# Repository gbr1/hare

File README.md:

# hare

An open source and open hardware implementation for 4-wheeled mobile robots.

It is compatible with ROS2 and DC brushed motors with encoder.

## Tech specs

- RP2040 MCU

- dual TB6612FNG motor drivers

- MPU6050 6DoF IMU

- LIS3MDL 3 axis magnetometer

- Power switch only for motors power supply

- 10-15V power input

- external connectors for I2C, debugger and UART

- compatibility with common motors with encoder (e.g. [moebiustech gearmotor](https://it.aliexpress.com/item/4000149449495.html?spm=a2g0o.store_pc_groupList.8148356.12.6b414f417HELfJ&pdp_npi=3%40dis%21EUR%21%E2%82%AC%2017%2C51%21%E2%82%AC%2016%2C64%21%21%21%21%21%40211b88ee16852754993946028e1b9d%2110000000459436942%21sh%21IT%210))

## License

The board is under **CC-4.0-BY-SA-NC** but ***dual licensing is available.***

<br>

For more info contact me.

## Links

- [firmware](https://github.com/gbr1/hare-arduino)

- [website](https://gbr1.github.io)

- [pizzarobotics](https://pizzarobotics.org)

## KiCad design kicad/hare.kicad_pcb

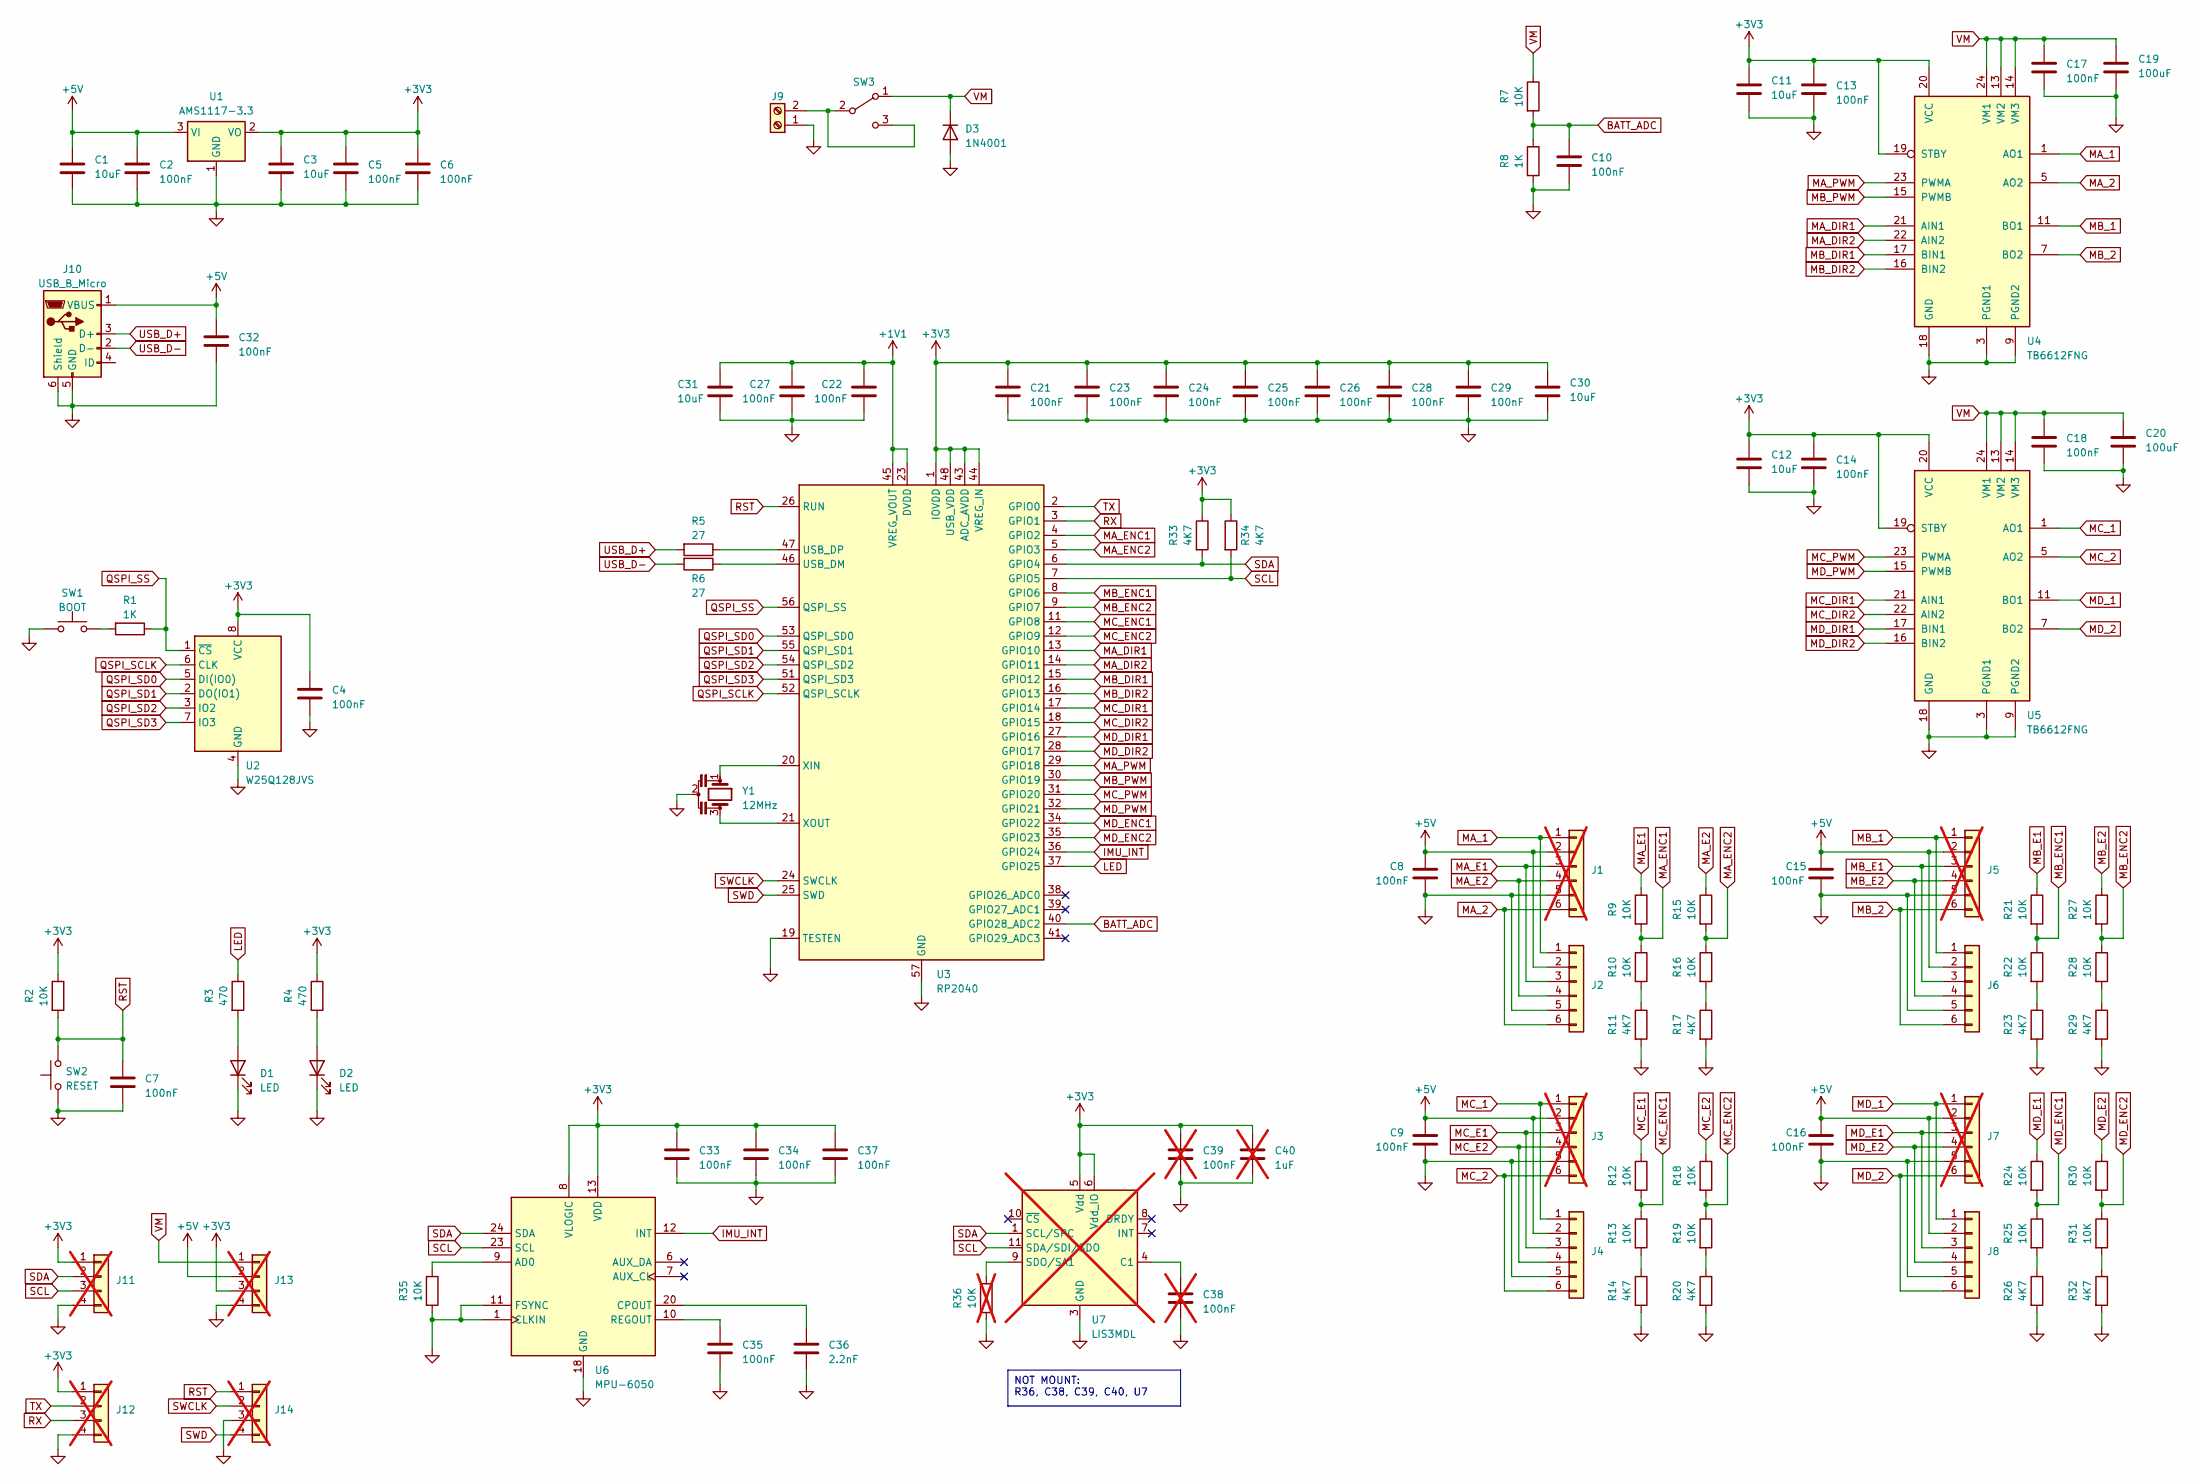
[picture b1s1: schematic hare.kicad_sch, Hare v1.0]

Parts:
C1, C3, C11, C12, C30, C31: 10uF; C_0603_1608Metric; LCSC Part # C85713
C2, C4, C5, C6, C7, C8, C9, C10, C13, C14, C15, C16, C17, C18, C21, C22, C23, C24, C25, C26, C27, C28, C29, C32, C33, C34, C35, C37: 100nF; C_0402_1005Metric; LCSC Part # C1525
C19, C20: 100uF; C_1210_3225Metric; LCSC Part # C90143
C36: 2.2nF; C_0402_1005Metric; LCSC Part # C106861
C38, C39: 100nF; C_0402_1005Metric; LCSC Part # C1525; not fitted
C40: 1uF; C_0402_1005Metric; LCSC Part # C913556; not fitted
D1: LED; LED_0603_1608Metric; LCSC Part # C72041
D2: LED; LED_0603_1608Metric; LCSC Part # C84263
D3: 1N4001; D_SMA; LCSC Part # C727079
J1, J3, J5, J7: PinHeader_1x06_P2.54mm_Vertical; not fitted
J2, J4, J6, J8: JST_PH_B6B-PH-K_1x06_P2.00mm_Vertical; LCSC Part # C131342
J9: TerminalBlock_Phoenix_MKDS-1,5-2-5.08_1x02_P5.08mm_Horizont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; LCSC Part # C8465
J10: USB_B_Micro; USB_Micro-B_Molex-105017-0001; LCSC Part # C136000
J11, J12, J13, J14: PinHeader_1x04_P2.54mm_Vertical; not fitted
R1, R8: 1K; R_0402_1005Metric; LCSC Part # C3015791
R2, R7, R9, R10, R12, R13, R15, R16, R18, R19, R21, R22, R24, R25, R27, R28, R30, R31, R35: 10K; R_0402_1005Metric; LCSC Part # C3015825
R3, R4: 470; R_0402_1005Metric; LCSC Part # C3015779
R5, R6: 27; R_0402_1005Metric; LCSC Part # C3017455
R11, R14, R17, R20, R23, R26, R29, R32, R33, R34: 4K7; R_0402_1005Metric; LCSC Part # C3015810
R36: 10K; R_0402_1005Metric; LCSC Part # C3015825; not fitted
SW1: BOOT; SW_Push_1P1T_NO_Vertical_Wuerth_434133025816; LCSC Part # C139797
SW2: RESET; SW_Push_1P1T_NO_Vertical_Wuerth_434133025816; LCSC Part # C139797
SW3: XKB-Connectivity-SS-12D10L5; LCSC Part # C319012
U1: AMS1117-3.3; SOT-223-3_TabPin2; LCSC Part # C6186
U2: W25Q128JVS; SOIC-8_5.23x5.23mm_P1.27mm; LCSC Part # C97521
U3: RP2040; QFN-56-1EP_7x7mm_P0.4mm_EP3.2x3.2mm; LCSC Part # C2040
U4, U5: TB6612FNG; SSOP-24_5.3x8.2mm_P0.65mm; LCSC Part # C141517
U6: MPU-6050; InvenSense_QFN-24_4x4mm_P0.5mm; LCSC Part # C24112
U7: LIS3MDL; LGA-12_2x2mm_P0.5mm; LCSC Part # C478483; not fitted
Y1: 12MHz; Resonator_SMD_Murata_CSTxExxV-3Pin_3.0x1.1mm; LCSC Part # C907957

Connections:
+1V1: C22.1, C27.1, C31.1, U3.23 (DVDD), U3.45 (VREG_VOUT), U3.50 (DVDD)
+3V3: C3.1, C4.1, C5.1, C6.1, C11.1, C12.1, C13.1, C14.1, C21.1, C23.1, C24.1, C25.1, C26.1, C28.1, C29.1, C30.1, C33.1, C34.1, C37.1, C39.1, C40.1, J11.1, J12.1, J13.3, R2.1, R4.1, R33.1, R34.1, U1.2 (VO), U2.8 (VCC), U3.1 (IOVDD), U3.10 (IOVDD), U3.22 (IOVDD), U3.33 (IOVDD), U3.42 (IOVDD), U3.43 (ADC_AVDD), U3.44 (VREG_IN), U3.48 (USB_VDD), U3.49 (IOVDD), U4.19 (STBY), U4.20 (VCC), U5.19 (STBY), U5.20 (VCC), U6.8 (VLOGIC), U6.13 (VDD), U7.5 (Vdd), U7.6 (Vdd_IO)
+5V: C1.1, C2.1, C8.1, C9.1, C15.1, C16.1, C32.1, J1.2, J2.2, J3.2, J4.2, J5.2, J6.2, J7.2, J8.2, J10.1 (VBUS), J13.2, U1.3 (VI)
BATT_ADC: C10.1, R7.2, R8.1, U3.40 (GPIO28_ADC2)
GND: C1.2, C2.2, C3.2, C4.2, C5.2, C6.2, C7.2, C8.2, C9.2, C10.2, C11.2, C12.2, C13.2, C14.2, C15.2, C16.2, C17.2, C18.2, C19.2, C20.2, C21.2, C22.2, C23.2, C24.2, C25.2, C26.2, C27.2, C28.2, C29.2, C30.2, C31.2, C32.2, C33.2, C34.2, C35.2, C36.2, C37.2, C38.2, C39.2, C40.2, D1.1 (K), D2.1 (K), D3.2 (A), J1.5, J2.5, J3.5, J4.5, J5.5, J6.5, J7.5, J8.5, J9.1, J10.5 (GND), J10.6 (Shield), J11.4, J12.4, J13.4, J14.3, R8.2, R11.2, R14.2, R17.2, R20.2, R23.2, R26.2, R29.2, R32.2, R35.2, R36.2, SW1.1, SW2.1, U1.1 (GND), U2.4 (GND), U3.19 (TESTEN), U3.57 (GND), U4.3 (PGND1), U4.4 (PGND1), U4.9 (PGND2), U4.10 (PGND2), U4.18 (GND), U5.3 (PGND1), U5.4 (PGND1), U5.9 (PGND2), U5.10 (PGND2), U5.18 (GND), U6.1 (CLKIN), U6.11 (FSYNC), U6.18 (GND), U7.2 (GND), U7.3 (GND), U7.12 (GND), Y1.2
IMU_INT: U3.36 (GPIO24), U6.12 (INT)
LED: R3.1, U3.37 (GPIO25)
MA_1: J1.1, J2.1, U4.1 (AO1), U4.2 (AO1)
MA_2: J1.6, J2.6, U4.5 (AO2), U4.6 (AO2)
MA_DIR1: U3.13 (GPIO10), U4.21 (AIN1)
MA_DIR2: U3.14 (GPIO11), U4.22 (AIN2)
MA_E1: J1.3, J2.3, R9.1
MA_E2: J1.4, J2.4, R15.1
MA_ENC1: R9.2, R10.1, U3.4 (GPIO2)
MA_ENC2: R15.2, R16.1, U3.5 (GPIO3)
MA_PWM: U3.29 (GPIO18), U4.23 (PWMA)
MB_1: J5.1, J6.1, U4.11 (BO1), U4.12 (BO1)
MB_2: J5.6, J6.6, U4.7 (BO2), U4.8 (BO2)
MB_DIR1: U3.15 (GPIO12), U4.17 (BIN1)
MB_DIR2: U3.16 (GPIO13), U4.16 (BIN2)
MB_E1: J5.3, J6.3, R21.1
MB_E2: J5.4, J6.4, R27.1
MB_ENC1: R21.2, R22.1, U3.8 (GPIO6)
MB_ENC2: R27.2, R28.1, U3.9 (GPIO7)
MB_PWM: U3.30 (GPIO19), U4.15 (PWMB)
MC_1: J3.1, J4.1, U5.1 (AO1), U5.2 (AO1)
MC_2: J3.6, J4.6, U5.5 (AO2), U5.6 (AO2)
MC_DIR1: U3.17 (GPIO14), U5.21 (AIN1)
MC_DIR2: U3.18 (GPIO15), U5.22 (AIN2)
MC_E1: J3.3, J4.3, R12.1
MC_E2: J3.4, J4.4, R18.1
MC_ENC1: R12.2, R13.1, U3.11 (GPIO8)
MC_ENC2: R18.2, R19.1, U3.12 (GPIO9)
MC_PWM: U3.31 (GPIO20), U5.23 (PWMA)
MD_1: J7.1, J8.1, U5.11 (BO1), U5.12 (BO1)
MD_2: J7.6, J8.6, U5.7 (BO2), U5.8 (BO2)
MD_DIR1: U3.27 (GPIO16), U5.17 (BIN1)
MD_DIR2: U3.28 (GPIO17), U5.16 (BIN2)
MD_E1: J7.3, J8.3, R24.1
MD_E2: J7.4, J8.4, R30.1
MD_ENC1: R24.2, R25.1, U3.34 (GPIO22)
MD_ENC2: R30.2, R31.1, U3.35 (GPIO23)
MD_PWM: U3.32 (GPIO21), U5.15 (PWMB)
unnamed: D1.2 (A), R3.2
unnamed: D2.2 (A), R4.2
unnamed: J9.2, SW3.2 (B), SW3.3 (C)
unnamed: R1.2, SW1.2
unnamed: R10.2, R11.1
unnamed: R13.2, R14.1
unnamed: R16.2, R17.1
unnamed: R19.2, R20.1
unnamed: R22.2, R23.1
unnamed: R25.2, R26.1
unnamed: R28.2, R29.1
unnamed: R31.2, R32.1
unnamed: R6.1, U3.46 (USB_DM)
unnamed: R5.1, U3.47 (USB_DP)
unnamed: U3.20 (XIN), Y1.1
unnamed: U3.21 (XOUT), Y1.3
unnamed: R35.1, U6.9 (AD0)
unnamed: C36.1, U6.20 (CPOUT)
unnamed: C35.1, U6.10 (REGOUT)
unnamed: C38.1, U7.4 (C1)
unnamed: R36.1, U7.9 (SDO/SA1)
QSPI_SCLK: U2.6 (CLK), U3.52 (QSPI_SCLK)
QSPI_SD0: U2.5 (DI(IO0)), U3.53 (QSPI_SD0)
QSPI_SD1: U2.2 (DO(IO1)), U3.55 (QSPI_SD1)
QSPI_SD2: U2.3 (IO2), U3.54 (QSPI_SD2)
QSPI_SD3: U2.7 (IO3), U3.51 (QSPI_SD3)
QSPI_SS: R1.1, U2.1 (~CS), U3.56 (QSPI_SS)
RST: C7.1, J14.1, R2.2, SW2.2, U3.26 (RUN)
RX: J12.3, U3.3 (GPIO1)
SCL: J11.3, R34.2, U3.7 (GPIO5), U6.23 (SCL), U7.11 (SDA/SDI/SDO)
SDA: J11.2, R33.2, U3.6 (GPIO4), U6.24 (SDA), U7.1 (SCL/SPC)
SWCLK: J14.2, U3.24 (SWCLK)
SWD: J14.4, U3.25 (SWD)
TX: J12.2, U3.2 (GPIO0)
USB_D+: J10.3 (D+), R5.2
USB_D-: J10.2 (D-), R6.2
VM: C17.1, C18.1, C19.1, C20.1, D3.1 (K), J13.1, R7.1, SW3.1 (A), U4.13 (VM2), U4.14 (VM3), U4.24 (VM1), U5.13 (VM2), U5.14 (VM3), U5.24 (VM1)

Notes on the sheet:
NOT MOUNT: R36, C38, C39, C40, U7

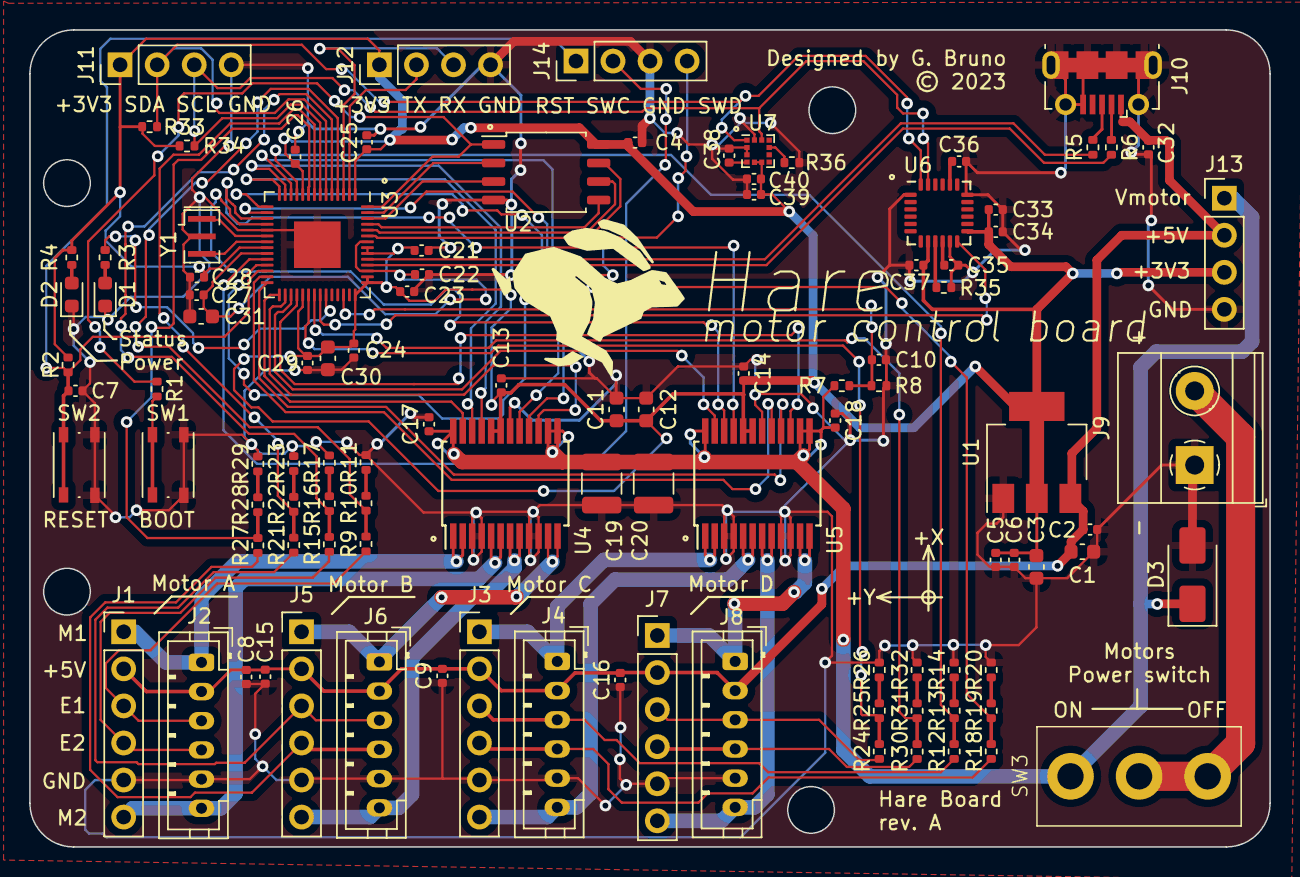
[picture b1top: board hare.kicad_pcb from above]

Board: 2 copper layers, 85.0 x 56.0 mm, 104 parts (0 on the bottom side), 80 nets.

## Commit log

2023-05-28 rev a

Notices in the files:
kicad/hare.kicad_pcb:
© 2023
